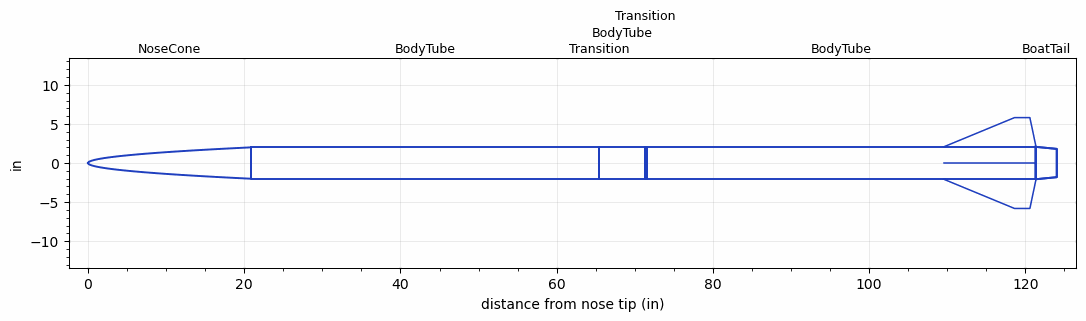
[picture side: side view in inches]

<RASAeroDocument>
 <FileVersion>2</FileVersion>
 <RocketDesign>
  <NoseCone>
   <Length>20.866</Length>
   <Diameter>4.0157</Diameter>
   <Shape>Power Law</Shape>
   <Location>0</Location>
   <PowerLaw>0.5</PowerLaw>
  </NoseCone>
  <BodyTube>
   <Length>44.49</Length>
   <Diameter>4.0157</Diameter>
   <Location>20.866</Location>
  </BodyTube>
  <Transition>
   <Length>0.0787</Length>
   <Diameter>4.1417</Diameter>
   <Location>65.356</Location>
   <RearDiameter>4.1417</RearDiameter>
  </Transition>
  <BodyTube>
   <Length>5.9055</Length>
   <Diameter>4.1417</Diameter>
   <Location>65.4347</Location>
  </BodyTube>
  <Transition>
   <Length>0.0787</Length>
   <Diameter>4.0157</Diameter>
   <Location>71.3402</Location>
   <RearDiameter>4.0157</RearDiameter>
  </Transition>
  <Transition>
   <Length>0.1968</Length>
   <Diameter>4.1496</Diameter>
   <Location>71.4189</Location>
   <RearDiameter>4.1496</RearDiameter>
  </Transition>
  <BodyTube>
   <Length>49.685</Length>
   <Diameter>4.1496</Diameter>
   <RailGuideDiameter>0.394</RailGuideDiameter>
   <RailGuideHeight>0.19685</RailGuideHeight>
   <Location>71.6157</Location>
   <BoattailLength>2.7165</BoattailLength>
   <BoattailRearDiameter>3.6221</BoattailRearDiameter>
   <Overhang>0.06099987</Overhang>
   <Fin>
    <Count>4</Count>
    <Chord>11.811</Chord>
    <Span>3.7401</Span>
    <SweepDistance>9.0551</SweepDistance>
    <TipChord>1.9685</TipChord>
    <Thickness>0.3149</Thickness>
    <Location>11.75</Location>
    <AirfoilSection>Hexagonal</AirfoilSection>
    <FX1>0.9843</FX1>
    <FX3>0.9843</FX3>
   </Fin>
  </BodyTube>
  <BoatTail>
   <Length>2.7165</Length>
   <Diameter>4.1496</Diameter>
   <RearDiameter>3.6221</RearDiameter>
   <Location>121.3007</Location>
  </BoatTail>
  <Surface>Smooth Paint</Surface>
  <ModifiedBarrowman>True</ModifiedBarrowman>
  <Turbulence>True</Turbulence>
  <UseBooster1>False</UseBooster1>
  <UseBooster2>False</UseBooster2>
 </RocketDesign>
 <LaunchSite>
  <Altitude>0</Altitude>
  <Pressure>0</Pressure>
  <RodAngle>5</RodAngle>
  <RodLength>39.37</RodLength>
  <Temperature>74</Temperature>
  <WindSpeed>4.47</WindSpeed>
 </LaunchSite>
 <Recovery>
  <Altitude1>1000</Altitude1>
  <Altitude2>1640.42</Altitude2>
  <DeviceType1>Parachute</DeviceType1>
  <DeviceType2>Parachute</DeviceType2>
  <Event1>True</Event1>
  <Event2>True</Event2>
  <Size1>29.52756</Size1>
  <Size2>78.7402</Size2>
  <EventType1>Apogee</EventType1>
  <EventType2>Altitude</EventType2>
  <CD1>0.8</CD1>
  <CD2>1.2</CD2>
 </Recovery>
 <SimulationList>
  <Simulation>
   <SustainerEngine>N1560-WH-MB-P  (CTI)</SustainerEngine>
   <SustainerLaunchWt>59.06</SustainerLaunchWt>
   <SustainerNozzleDiameter>2.44</SustainerNozzleDiameter>
   <SustainerCG>85.04</SustainerCG>
   <SustainerIgnitionDelay>0</SustainerIgnitionDelay>
   <Booster1SeparationDelay>0</Booster1SeparationDelay>
   <Booster1IgnitionDelay>0</Booster1IgnitionDelay>
   <IncludeBooster1>False</IncludeBooster1>
   <Booster2Delay>0</Booster2Delay>
   <IncludeBooster2>False</IncludeBooster2>
   <TimetoApogee>42.13894</TimetoApogee>
   <MaxAltitude>31159.92</MaxAltitude>
   <MaxVelocity>1668.572</MaxVelocity>
   <OptimumWt>28.28303</OptimumWt>
   <OptimumMaxAlt>28.28303</OptimumMaxAlt>
  </Simulation>
 </SimulationList>
</RASAeroDocument>
